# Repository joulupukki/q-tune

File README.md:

# Q-Tune Chromatic Tuner
This is an in-progress project with the goal of creating a fully open-source chromatic tuner in a standard pedal enclosure for use on pedalboards and based on the ESP32 MCU.

The project uses the Q DSP Library for frequency detection and LVGL 9 for the graphical user interface.

The project now uses a [Waveshare ESP32-S3 Touch 2.8" 240x320](https://www.waveshare.com/product/mcu-tools/development-boards/esp32/esp32-s3-touch-lcd-2.8.htm?sku=27690) screen because of its clean cover glass that's already attached. It helps make a very professional look in a guitar pedal. Currently the capacitive touch isn't being used.

The project first used a Heltec ESP32-S3 with a smaller display, graduated to the Cheap Yellow Display (ESP32-2432S028R/ESP32-WROOM-32), and is now using the Waveshare.

## Setup

1. Install Visual Studio Code
2. Install the Visual Studio Code ESP-IDF extension
3. Configure the ESP-IDF extension by using the express or advanced mode
    - Be sure to choose **v5.3** as the version of ESP-IDF to use
    - You may need to use advanced mode to be able to select the correct location for python3
    - If pip error, navigate to: C:\Espressif\tools\idf-python\3.11.2> and run: python -m ensurepip --upgrade
4. Make sure you have `git` installed
5. Clone this github project
6. From a terminal go into the project and do this:
    ```
    git submodule update --init --recursive
    ```
7. Open the `q-tune` folder in VS Code
8. Set your ESP32 target (esp32s3)
    - Open the Command Palette (Command+Shift+P on a Mac) and select `ESP-IDF: Set Espressif Device Target`
    - Select `esp32s3`
    - Select the `ESP32-S3 chip (via ESP-PROG)` option
9. Select the port to use
    - Plug in your ESP32 dev board and wait for a few seconds
    - Open the Command Palette (Command+Shift+P on a Mac) and select `ESP-IDF: Select Port to Use (COM, tty, usbserial)`
    - Select your port from the drop-down list that appears
    - Windows Only: If you receive an error while trying to locate the serial/COM port that your ESP32 is connected to (or it doesn't show up), you may need to install the driver for the CH340C UART chip that the ESP32-CYD uses for USB communication. The driver is available from the manufacturer here: https://www.wch-ic.com/downloads/CH341SER_ZIP.html
        - After installing the driver and connecting the CYD, re-run the "Select Port" command
10. Attempt to build the software
    - Use the Command Palette and select `ESP-IDF: Build your Project`
11. Assuming step #9 worked, Build and install the software
    - Use the Command Palette and select `ESP-IDF: Build, Flash, and Start a Monitor on your Device`
    - To stop monitoring the output, press Control+T, then X

## Demo

Better smoothing and pre-amp circuit 19 Mar 2025:

We're getting closer to releasing the first version. Here's a demo of how it's looking on 13 Mar 2025:

Here's a simple demo of how the project is coming along as of 10 Dec 2024:

Here's an older demo, more of a proof-of-concept on a smaller screen using a Heltec ESP32-S3 (20 Aug 2024):

## License

This software is licensed under the GNU General Public License (GPL) for open-source use. A commercial license is available for those who wish to use this software in proprietary or closed-source projects. For more details, please contact btimothy [at] gmail [dot] com.

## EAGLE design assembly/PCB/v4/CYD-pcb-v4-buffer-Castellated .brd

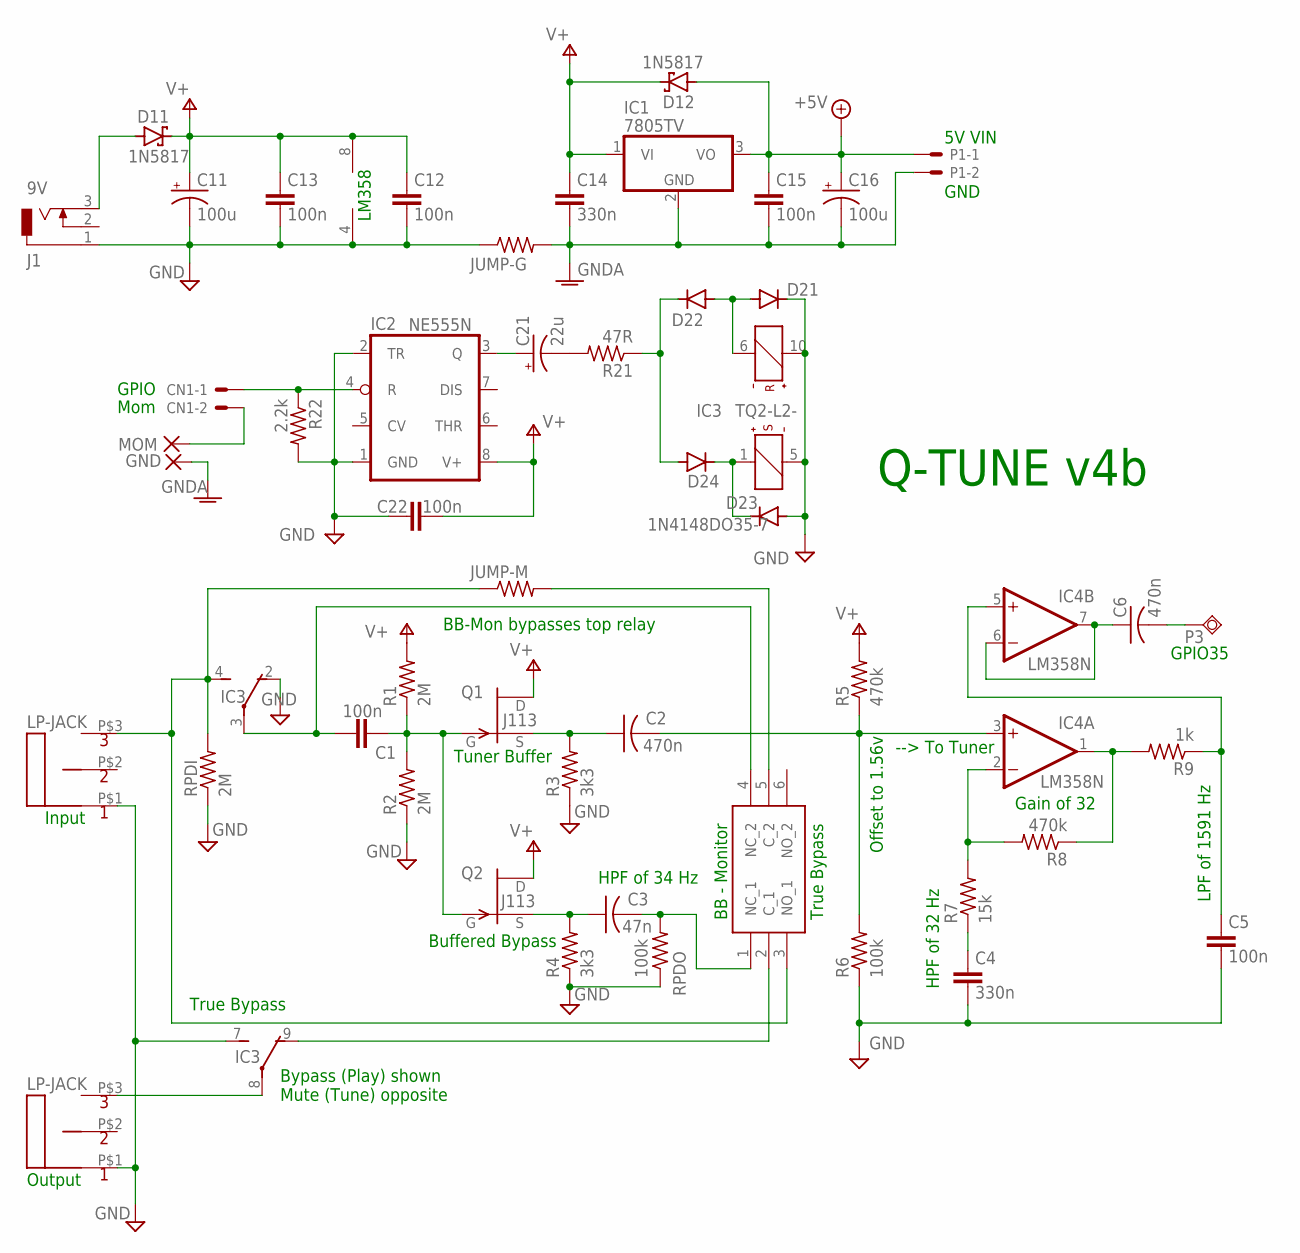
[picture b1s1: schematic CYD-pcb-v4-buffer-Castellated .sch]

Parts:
C1, C5, C12, C13, C15, C22: 100n; C050-024X044
C2, C6: 470n; C050-035X075
C3: 47n; C050-035X075
C4, C14: 330n; C050-024X044
C11, C16: 100u; E2,5-6
C21: 22u; E2,5-6
CN1: 22-23-2021
D11, D12: 1N5817; DO41-7.6
D21, D22, D23, D24: 1N4148DO35-7; DO35-7
GND: WIREPAD1,6/0,9; 1,6/0,9
IC1: 7805TV; TO220V
IC2: NE555N; DIL08
IC3: TQ2-L2-; TQ2
IC4: LM358N; DIL08
INPUTJACK: LPJACK-DEVICE; LPJACK-FOOTPRINT
J1: 9V; DCJ0303
JUMP-G: *; 0207/7
JUMP-M: 1; 0207/7
MOM: WIREPAD1,6/0,9; 1,6/0,9
OUTPUTJACK: LPJACK-DEVICE; LPJACK-FOOTPRINT
P1: 22-23-2021
P3: TPSQPAD1-13Y; P1-13Y
Q1, Q2: J113; TO92-
R1, R2: 2M; 0207/7
R3, R4: 3k3; 0207/7
R5, R8: 470k; 0207/7
R6: 100k; 0207/7
R7: 15k; 0207/7
R9: 1k; 0207/7
R21: 47R; 0207/7
R22: 2.2k; 0207/7
RPDI: 2M; 0207/7
RPDO: 100k; 0207/7
SW1: JS202011AQN

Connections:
+5V: C15.1, C16.+, D12.A, IC1.3 (VO), P1.1
GND: C4.2, C5.2, C11.-, C12.2, C13.2, C22.1, D21.C, D23.A, IC2.1 (GND), IC2.2 (TR), IC3.2 (O), IC3.5 (-), IC3.7 (S), IC3.10 (+), IC4.4 (V-), INPUTJACK.P$1 (1), J1.1, JUMP-G.1, OUTPUTJACK.P$1 (1), R2.1, R3.1, R4.1, R6.1, R22.2, RPDI.1, RPDO.1
GNDA: C14.2, C15.2, C16.-, GND.1, IC1.2 (GND), JUMP-G.2, P1.2
unnamed: CN1.1, IC2.4 (R), R22.1
unnamed: C3.2, RPDO.2, SW1.1 (NC_1)
unnamed: C2.1, Q1.2 (S), R3.2
unnamed: C2.2, IC4.3 (+IN), R5.1, R6.2
unnamed: IC4.2 (-IN), R7.2, R8.2
unnamed: IC4.1 (OUT), R8.1, R9.2
unnamed: D22.C, D24.A, R21.1
unnamed: C6.1, IC4.6 (-IN), IC4.7 (OUT)
unnamed: CN1.2, MOM.1
unnamed: D11.A, J1.3
unnamed: C4.1, R7.1
unnamed: D23.C, D24.C, IC3.1 (+)
unnamed: D21.A, D22.A, IC3.6 (-)
unnamed: C1.2, IC3.3, SW1.4 (NC_2)
unnamed: C21.+, IC2.3 (Q)
unnamed: C21.-, R21.2
unnamed: C5.1, IC4.5 (+IN), R9.1
unnamed: C1.1, Q1.1 (G), Q2.1 (G), R1.1, R2.2
unnamed: C3.1, Q2.2 (S), R4.2
unnamed: IC3.8, OUTPUTJACK.P$3 (3)
unnamed: IC3.9 (O), SW1.2 (C_1)
unnamed: JUMP-M.2, SW1.5 (C_2)
unnamed: C6.2, P3.TP
unnamed: IC3.4 (S), INPUTJACK.P$3 (3), JUMP-M.1, RPDI.2, SW1.3 (NO_1)
V+: C11.+, C12.1, C13.1, C14.1, C22.2, D11.C, D12.C, IC1.1 (VI), IC2.8 (V+), IC4.8 (V+), Q1.3 (D), Q2.3 (D), R1.2, R5.2

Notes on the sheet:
Input
Output
Mom
GPIO
GND
5V VIN
Gain of 32
HPF of 32 Hz
LPF of 1591 Hz
Offset to 1.56v
--> To Tuner
Q-TUNE v4b
GPIO35
LM358
Tuner Buffer
Buffered Bypass
Bypass (Play) shown Mute (Tune) opposite
True Bypass
BB - Monitor
BB-Mon bypasses top relay
HPF of 34 Hz

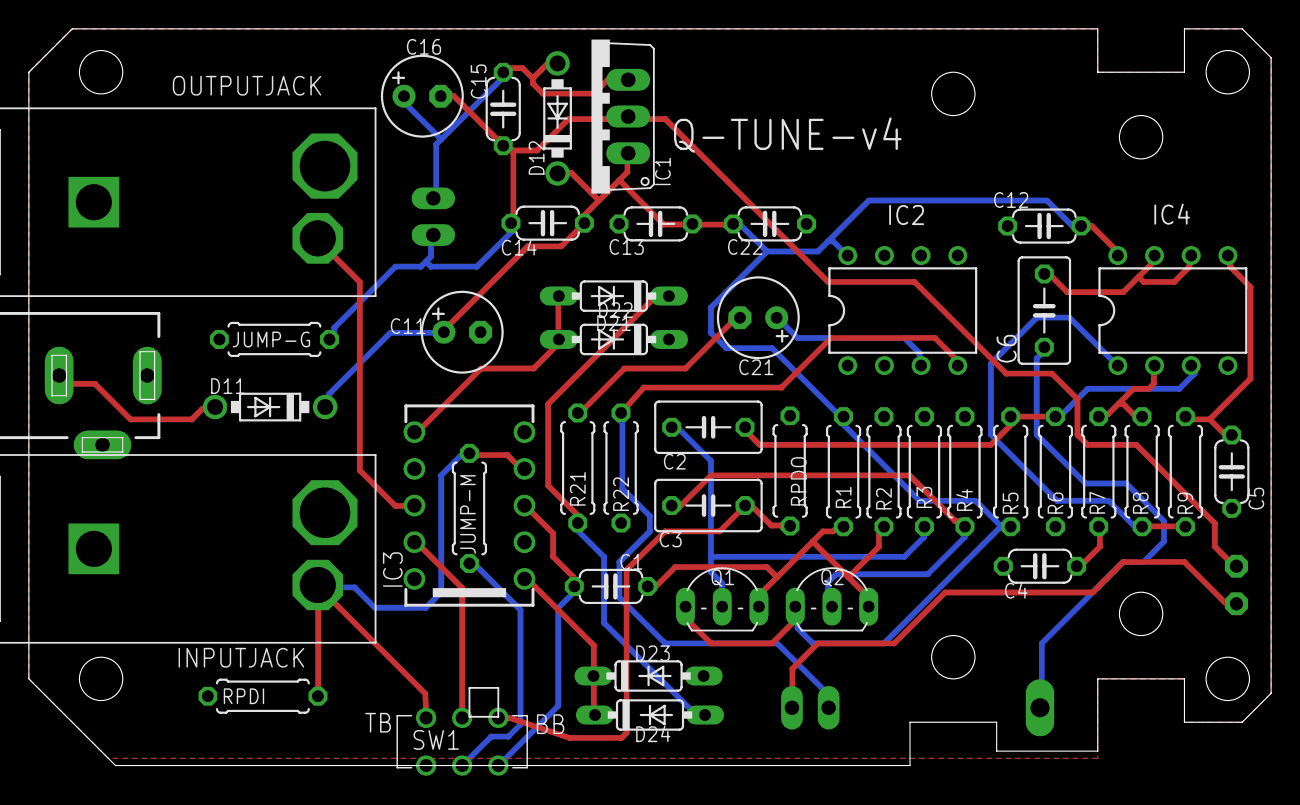
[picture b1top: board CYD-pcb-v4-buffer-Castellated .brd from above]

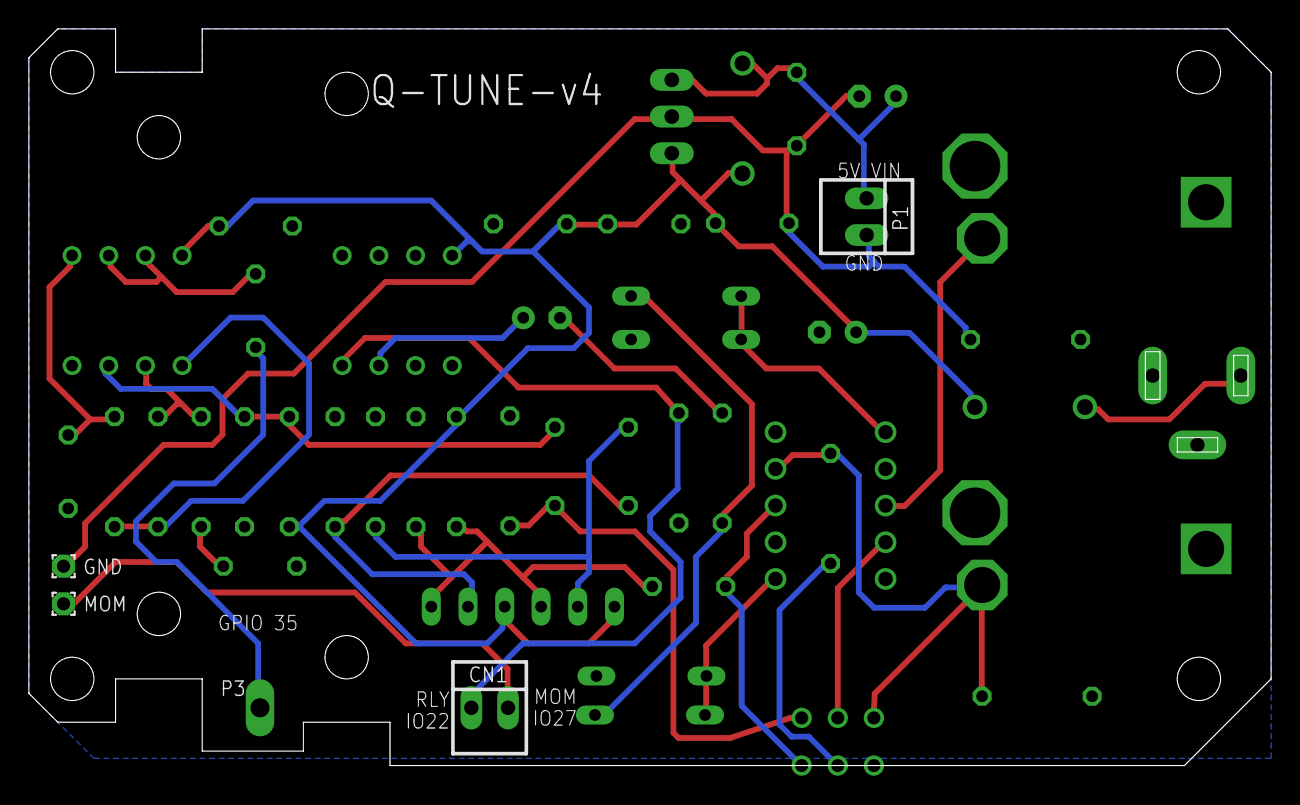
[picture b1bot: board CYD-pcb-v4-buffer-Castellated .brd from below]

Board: 2 copper layers, 86.0 x 51.0 mm, 50 parts (4 on the bottom side), 28 nets.

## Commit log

2025-02-05 touch calib experiment
2025-02-05 Switch the backlight control frequency from 5kHz to 30kHz to avoid noise
2025-02-05 Switch the backlight control frequency from 5kHz to 30kHz to avoid noise (#49)
2025-02-06 Add partial implementation of controlling settings with FS
    This fix passes foot switch presses on to the gui task and
    also to the User Settings. You can now advance through menu
    settings with a single press.
    Still left to be done is supporting double-press to send a
    press event to a button.
    Long press when in tuning mode to activate user settings.
2025-02-06 Implement the double-press so it works in user settings
2025-02-06 Support double-press only in settings
    This keeps the normal press fast when switching between tuning and
    true bypass mode.
2025-02-06 Set the backlight to 0% in true bypass mode
2025-02-06 Use LVGL group for focused navigation
2025-02-07 Adjust the in-tune threshold user setting to work with the foot switch
2025-02-07 Use radio buttons for choosing the tuner mode/UI
2025-02-07 Use radio buttons to set the display brightness
2025-02-07 Make color selection in user settings possible with foot switch
2025-02-07 Use radio buttons for choosing initial state of tuner
2025-02-07 Use radio buttons to change display orientation
2025-02-07 Make the Factory Reset buttons accessible by foot switch
2025-02-07 Use a foot switch to navigate user settings (#51)
    * Add partial implementation of controlling settings with FS
    This fix passes foot switch presses on to the gui task and
    also to the User Settings. You can now advance through menu
    settings with a single press.
    Still left to be done is supporting double-press to send a
    press event to a button.
2025-02-10 Add a median filter to the frequency output to smooth it a little
2025-02-10 Add the GPL header to the Median Filter file
2025-02-10 Add q signal conditioner and a median filter for smoother tuning output (#54)
    * Add a median filter to the frequency output to smooth it a little
    * Enable the qLib signal conditioner on the input
2025-02-23 Update the way the UI works when audio signal drops off
2025-02-23 Update the way the UI works when audio signal drops off (#58)
2025-02-23 Bump to v1.0.4
2025-02-23 Make the correct version show up on the About screen
2025-02-23 Add a new tuner UI called "Attitude" (Attitude Indicator)
    Also:
    - Bumped the cents and frequency labels to 18pt (from 14pt)
    - Fixed an issue that was making the UI jump around (disabled
    scrolling on the main screen)
2025-02-23 Add a new tuning UI called "Attitude" (like an airplane's Attitude Indicator) (#60)
    * Make the correct version show up on the About screen
    * Add a new tuner UI called "Attitude" (Attitude Indicator)
    Also:
    - Bumped the cents and frequency labels to 18pt (from 14pt)
    - Fixed an issue that was making the UI jump around (disabled
    scrolling on the main screen)
2025-02-26 Bump to v1.0.5
2025-02-27 Add support for monitoring mode
    Also adjusts display resolution on attitude tuner to move a little
    more than 1px per cent.
2025-02-27 Add support for monitoring mode (#62)
    Also adjusts display resolution on attitude tuner to move a little
    more than 1px per cent.
2025-02-27 Bump to v1.0.6
2025-03-05 Add new tuner UI that's a note quiz
2025-03-05 Use the right GPIO for the momentary switch
2025-03-05 Update the web installer helper script
2025-03-05 Bump to v1.0.7
2025-03-06 Improve the note quiz tuning display
2025-03-06 Bump to v2.0.0 in prep for switching to the EBD4 Waveshare
2025-03-09 Initial stab at switching Waveshare ESP32-S3-Touch-LCD-2.8B (EBD4)
2025-03-09 Bump to v1.0.8
2025-03-09 Use larger fonts on the Needle tuner
2025-03-09 Use larger fonts on the Strobe tuner
2025-03-10 Rework strobe tuner UI to work with EBD4
2025-03-10 Switch the font files to a format that's closer to RGB565
2025-03-10 Use DMA for the graphics buffers
2025-03-10 Move timer handler *after* doing all LVGL work in the loop
    Also change the lcd to use 2 buffers. I think it was already doing
    this, but just in case.
2025-03-11 Restore using 3 arcs for the Strobe tuner
2025-03-11 Clean up the display interface code a bit
2025-03-11 Improve CPU performance of the note quiz sitting idle
2025-03-11 Add a little cleanup
2025-03-11 Change the freq detector to use RTOS queues to publish freq info
2025-03-11 Use a queue length of 1 for the frequency info
2025-03-11 Use RTOS queue for managing the tuner state
2025-03-11 Remove esp_lvgl_port dependency for now
2025-03-11 Adjust frame buffer and remove some old semaphore for tuner state
2025-03-12 Partially implement switch to EBD2
2025-03-13 Make EBD2 work with ESP LVGL Port
2025-03-13 Fix up the attitude and strobe for 1x screen size
2025-03-13 Attempt to make the ADS1015 work
2025-03-14 Get Q-Tune working on EBD2 with ADC2 Channel 4
2025-03-14 Get backlight level working on EBD2
2025-03-14 Implement screen rotation with EBD2
2025-03-15 Added some work on the touch controller but keep it disabled
    Things don't work as well as they ought to and it causes crashing.
2025-03-15 Make the sharp image show back up in the strobe tuner
    Also add and comment out some code that uses calibrated ADC readings.
2025-03-15 Update the README for EBD2
2025-03-15 Switch to Waveshare ESP32-S3 Touch 2.8" (240x320) (#63)
    * Add new tuner UI that's a note quiz
    * Use the right GPIO for the momentary switch
    * Update the web installer helper script
    * Bump to v1.0.7
    * Improve the note quiz tuning display
    * Bump to v2.0.0 in prep for switching to the EBD4 Waveshare
2025-03-15 Fix up a code merge
2025-03-15 Switch to ADC2_CH7 (GPIO18) because GPIO15 is a strapping pin according to ESP32 tech ref
2025-03-17 Update the target note code to be more accurate
2025-03-17 Comment out some debug output printing
2025-03-18 Adjust the noise floor value
2025-03-18 Send target frequency and octave info to the tuning interfaces
2025-03-18 Add a new demo video
2025-03-18 Fix the latest demo video thumbnail image
2025-03-18 Fix the thumbnail image one more time
2025-03-19 Fix use of 1EU filter and also improve general smoothing
    A frequency is no longer reported to the UI unless a target note
    is seen more than once in a row. This helps prevent too much
    jumping around in the UI.
    I also messed around with the 1EU filter for getting the UI to
    feel more smooth. Right now pitch detection is using two 1EU filters
    and a moving average to smooth the detected frequency.
2025-03-19 Fix attitude tuner and use exp smoother too
    Also adds an additional demo video and turns off the LVGL perf info.
2025-03-25 Add support for the buffer type relay (true/buffered bypass)
2025-03-25 Add support for the buffer type relay (true/buffered bypass) (#67)
2025-03-30 Add new tuning UI called "Record Time"
2025-03-30 Bump to v2.1.0
2025-03-30 Add new tuning UI called "Record Time" (#69)
2025-03-30 Bump to v2.1.1
2025-03-30 Adjust the sensitivity of the strobe
2025-03-30 Bump to v2.1.2
2025-03-31 Remove the unused "hardware" directory from the list of includes
2025-03-31 Make sure Montserrat 18 is enabled
2025-04-01 Unmute inside bypass type settings screen
    This makes it so you can hear the difference more easily when switching
    between buffered bypass and true bypass mode without having to exit the
    settings screen.
2025-04-03 Use C malloc to prevent LVGL from freezing
    Also rearrange when the title of the record is rotated so that
    there isn't glitching.
2025-04-03 Change the in-tune indicator on record time for white
2025-04-03 Keep bypass type correct when turning on/off monitoring mode
    This also moves the UserSettings into a static reference (extern)
    variable instead of passing it all around in all the callbacks.
2025-04-03 Keep bypass type correct when turning on/off monitoring mode (#71)
    This also moves the UserSettings into a static reference (extern)
    variable instead of passing it all around in all the callbacks.
2025-04-13 Modify the double press and long press behavior in settings
    Long press now activates the focused button. Double press moves the
    focus to the previous item in the focus group. When you exit a screen
    it will automatically focus the Back/Exit button as a convenience.
2025-04-13 Modify the double press and long press behavior in settings (#72)
    Long press now activates the focused button. Double press moves the
    focus to the previous item in the focus group. When you exit a screen
    it will automatically focus the Back/Exit button as a convenience.
2025-04-13 Remove the exponential and moving avg smoother (faster)
2025-04-13 Prevent a crash when setting note name after switching to bypass
    If you were playing a note, switched to bypass mode (screen turns
    off) and then the note stopped playing, the timer to fade the note
    to none was firing on the UI that was already deleted from memory.
2025-04-13 Update the installer script for the new website repo
2025-04-13 Bump to v2.1.3
2025-04-19 Show in-tune threshold on the strobe tuner by changing arcs color
2025-04-19 Show in-tune threshold on the strobe tuner by changing arcs color (#74)
